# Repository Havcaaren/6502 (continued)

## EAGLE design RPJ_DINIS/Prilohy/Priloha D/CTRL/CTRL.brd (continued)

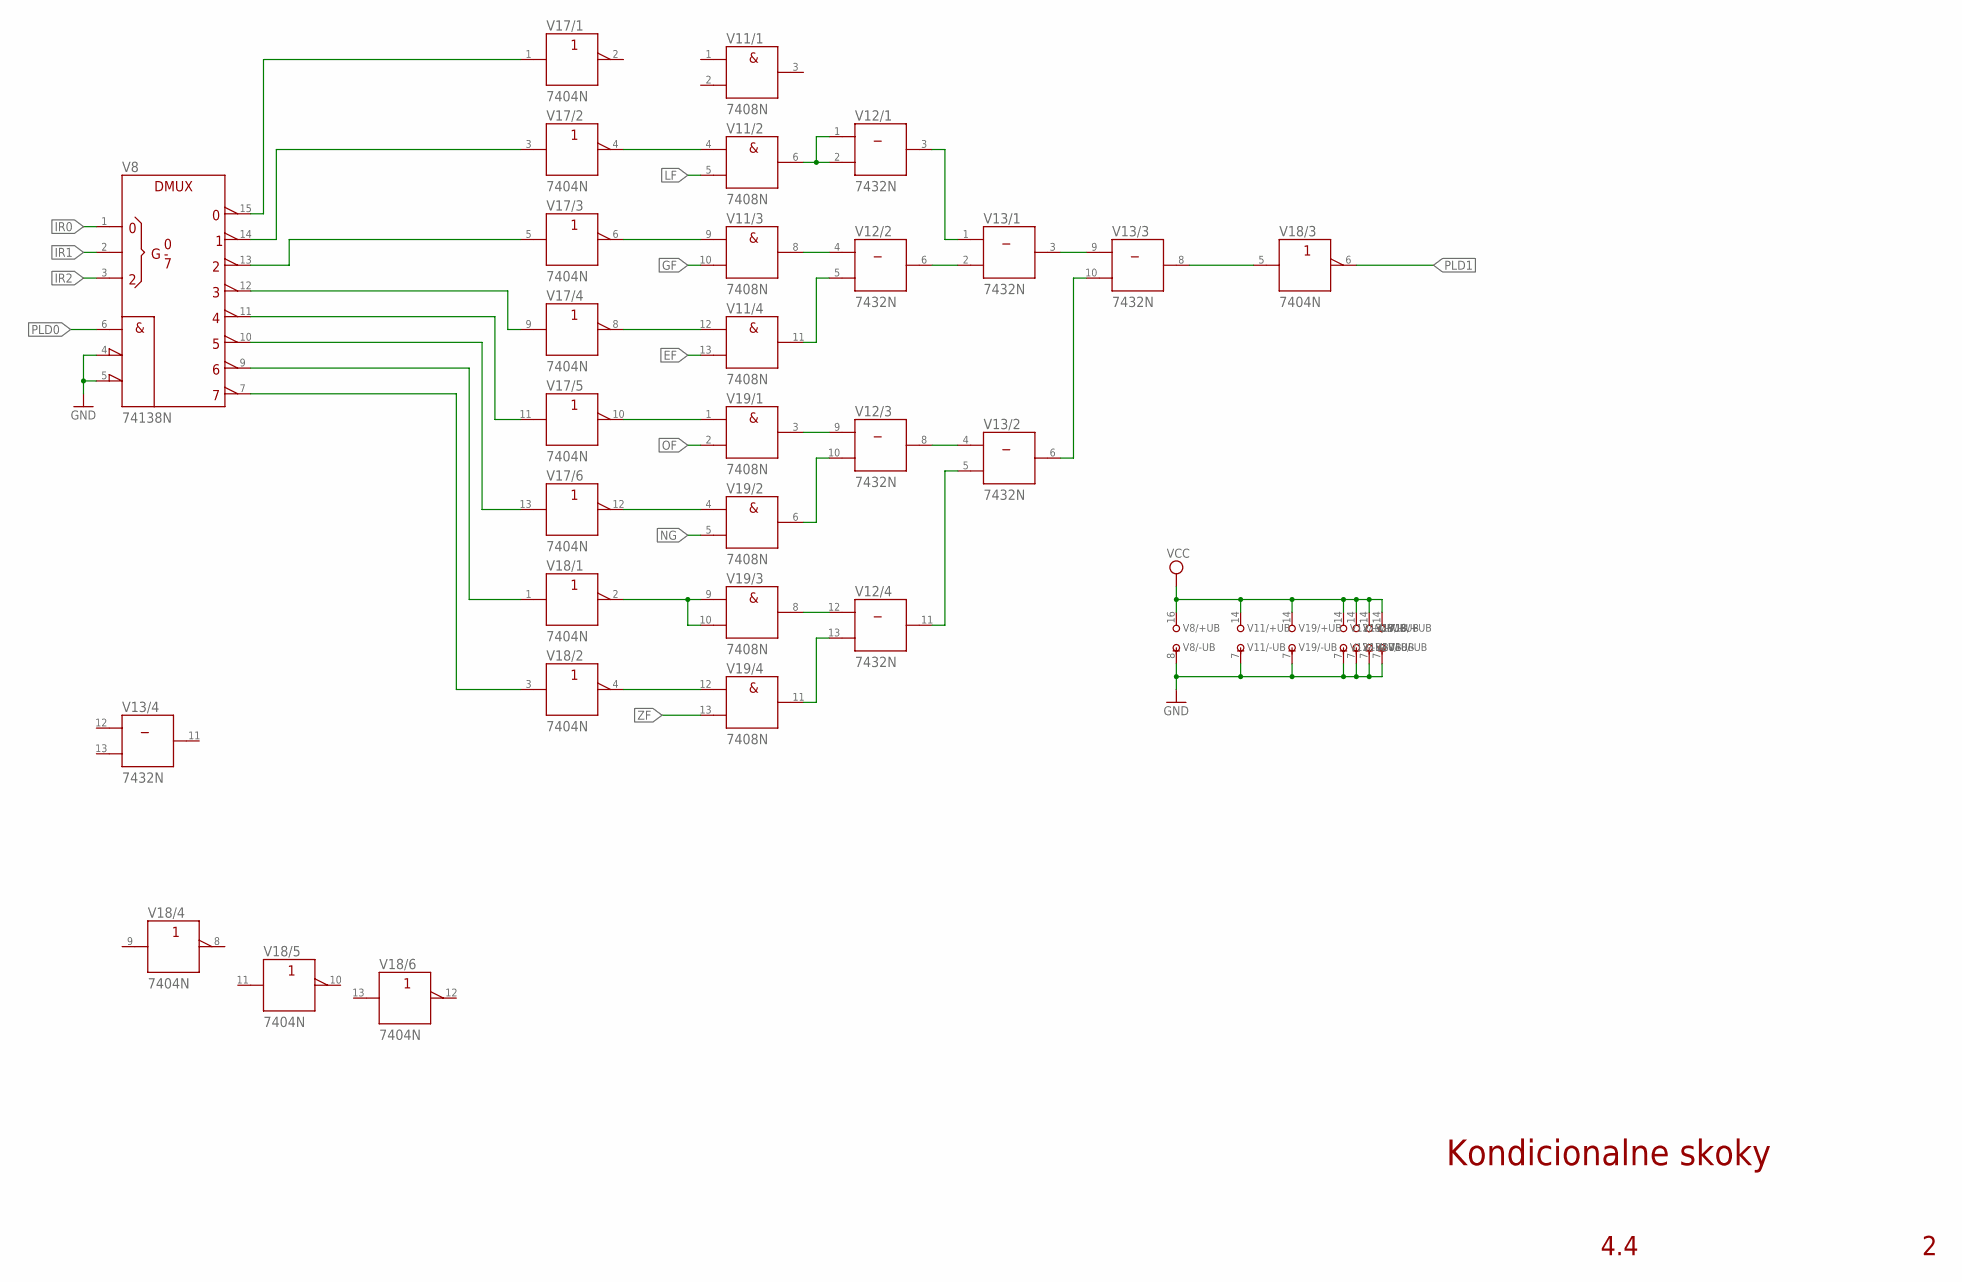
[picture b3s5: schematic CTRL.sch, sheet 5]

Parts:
V8: 74138N; DIL16
V11, V19: 7408N; DIL14
V12, V13: 7432N; DIL14
V17, V18: 7404N; DIL14

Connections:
EF: V11.13 (B); also elsewhere on the board
GF: V11.10 (B); also elsewhere on the board
GND: V8.4 (!G2A), V8.5 (!G2B), V8.8 (-UB), V11.7 (-UB), V12.7 (-UB), V13.7 (-UB), V17.7 (-UB), V18.7 (-UB), V19.7 (-UB); also elsewhere on the board
IR0: V8.1 (A); also elsewhere on the board
IR1: V8.2 (B); also elsewhere on the board
IR2: V8.3 (C); also elsewhere on the board
LF: V11.5 (B); also elsewhere on the board
unnamed: V18.2 (Y), V19.9 (A), V19.10 (B)
unnamed: V18.4 (Y), V19.12 (A)
unnamed: V17.12 (Y), V19.4 (A)
unnamed: V17.10 (Y), V19.1 (A)
unnamed: V11.12 (A), V17.8 (Y)
unnamed: V11.9 (A), V17.6 (Y)
unnamed: V11.4 (A), V17.4 (Y)
unnamed: V8.15 (Y0), V17.1 (A)
unnamed: V8.14 (Y1), V17.3 (A)
unnamed: V8.13 (Y2), V17.5 (A)
unnamed: V8.12 (Y3), V17.9 (A)
unnamed: V8.11 (Y4), V17.11 (A)
unnamed: V8.10 (Y5), V17.13 (A)
unnamed: V8.9 (Y6), V18.1 (A)
unnamed: V8.7 (Y7), V18.3 (A)
unnamed: V13.8 (Y), V18.5 (A)
unnamed: V12.11 (Y), V13.5 (B)
unnamed: V12.8 (Y), V13.4 (A)
unnamed: V12.3 (Y), V13.1 (A)
unnamed: V12.6 (Y), V13.2 (B)
unnamed: V13.3 (Y), V13.9 (A)
unnamed: V13.6 (Y), V13.10 (B)
unnamed: V11.6 (Y), V12.1 (A), V12.2 (B)
unnamed: V11.8 (Y), V12.4 (A)
unnamed: V11.11 (Y), V12.5 (B)
unnamed: V12.9 (A), V19.3 (Y)
unnamed: V12.10 (B), V19.6 (Y)
unnamed: V12.13 (B), V19.11 (Y)
unnamed: V12.12 (A), V19.8 (Y)
NG: V19.5 (B); also elsewhere on the board
OF: V19.2 (B); also elsewhere on the board
PLD0: V8.6 (G1); also elsewhere on the board
PLD1: V18.6 (Y); also elsewhere on the board
VCC: V8.16 (+UB), V11.14 (+UB), V12.14 (+UB), V13.14 (+UB), V17.14 (+UB), V18.14 (+UB), V19.14 (+UB); also elsewhere on the board
ZF: V19.13 (B); also elsewhere on the board

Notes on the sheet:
4.4
Kondicionalne skoky

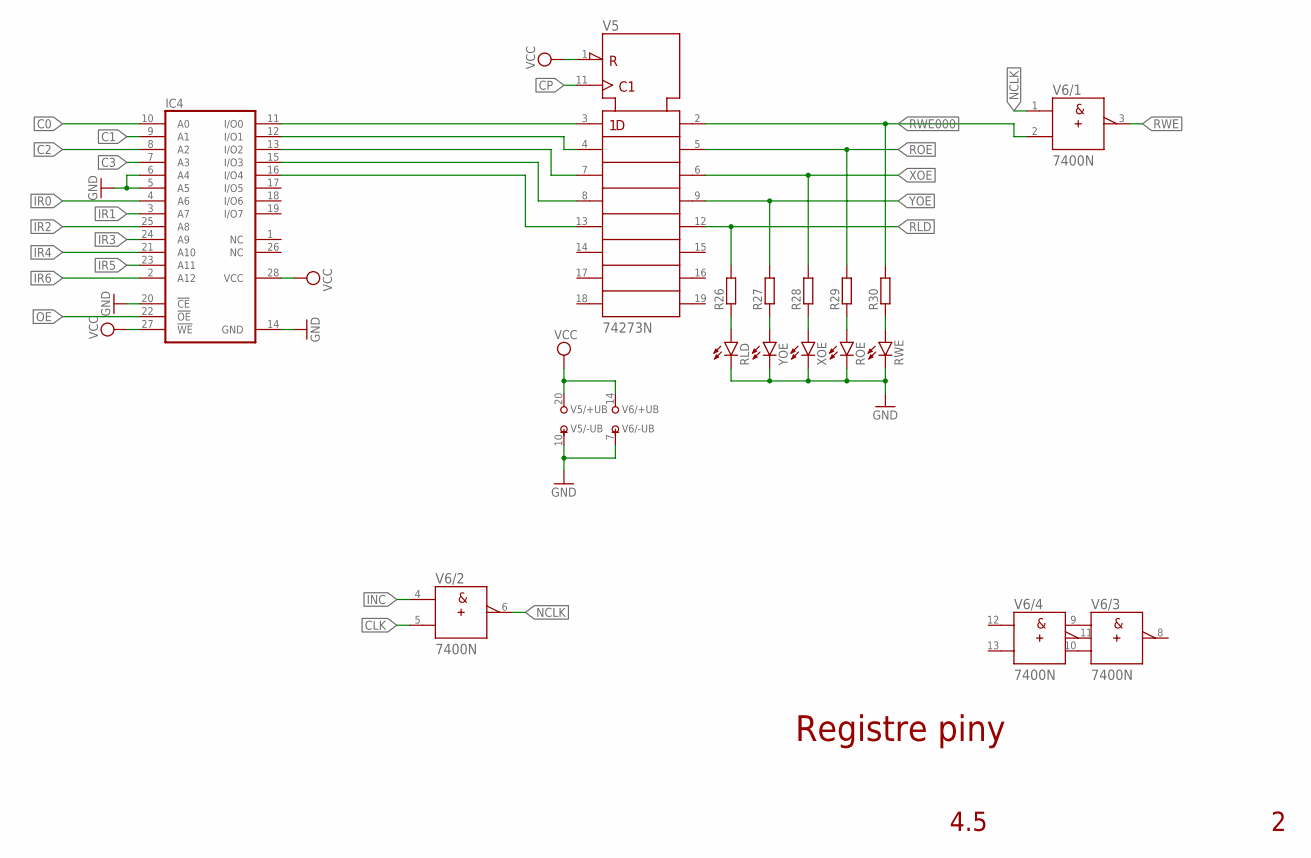
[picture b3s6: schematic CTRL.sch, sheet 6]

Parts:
IC4: 28C64C; DIL28-6
R26, R27, R28, R29, R30: R-EU_0204/7; 0204/7
RLD: LED5MM
ROE: LED5MM
RWE: LED5MM
V5: 74273N; DIL20
V6: 7400N; DIL14
XOE: LED5MM
YOE: LED5MM

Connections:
C0: IC4.10 (A0); also elsewhere on the board
C1: IC4.9 (A1); also elsewhere on the board
C2: IC4.8 (A2); also elsewhere on the board
C3: IC4.7 (A3); also elsewhere on the board
CLK: V6.5 (B); also elsewhere on the board
CP: V5.11 (CLK); also elsewhere on the board
GND: IC4.5 (A5), IC4.6 (A4), IC4.14 (GND), IC4.20 (!CE), RLD.K (C), ROE.K (C), RWE.K (C), V5.10 (-UB), V6.7 (-UB), XOE.K (C), YOE.K (C); also elsewhere on the board
INC: V6.4 (A); also elsewhere on the board
IR0: IC4.4 (A6); also elsewhere on the board
IR1: IC4.3 (A7); also elsewhere on the board
IR2: IC4.25 (A8); also elsewhere on the board
IR3: IC4.24 (A9); also elsewhere on the board
IR4: IC4.21 (A10); also elsewhere on the board
IR5: IC4.23 (A11); also elsewhere on the board
IR6: IC4.2 (A12); also elsewhere on the board
unnamed: IC4.16 (I/O4), V5.13 (5D)
unnamed: R26.1, RLD.A
unnamed: R27.1, YOE.A
unnamed: R28.1, XOE.A
unnamed: R29.1, ROE.A
unnamed: R30.1, RWE.A
NCLK: V6.1 (A), V6.6 (Y); also elsewhere on the board
OE: IC4.22 (!OE); also elsewhere on the board
RLD: R26.2, V5.12 (5Q); also elsewhere on the board
ROE: R29.2, V5.5 (2Q); also elsewhere on the board
RWE: V6.3 (Y); also elsewhere on the board
RWE000: R30.2, V5.2 (1Q), V6.2 (B)
VCC: IC4.27 (!WE), IC4.28 (VCC), V5.1 (!CLR), V5.20 (+UB), V6.14 (+UB); also elsewhere on the board
XCP0: IC4.11 (I/O0), V5.3 (1D)
XOE: R28.2, V5.6 (3Q); also elsewhere on the board
XOE0: IC4.12 (I/O1), V5.4 (2D)
YCP0: IC4.13 (I/O2), V5.7 (3D)
YOE: R27.2, V5.9 (4Q); also elsewhere on the board
YOE0: IC4.15 (I/O3), V5.8 (4D)

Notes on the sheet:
4.5
Registre piny

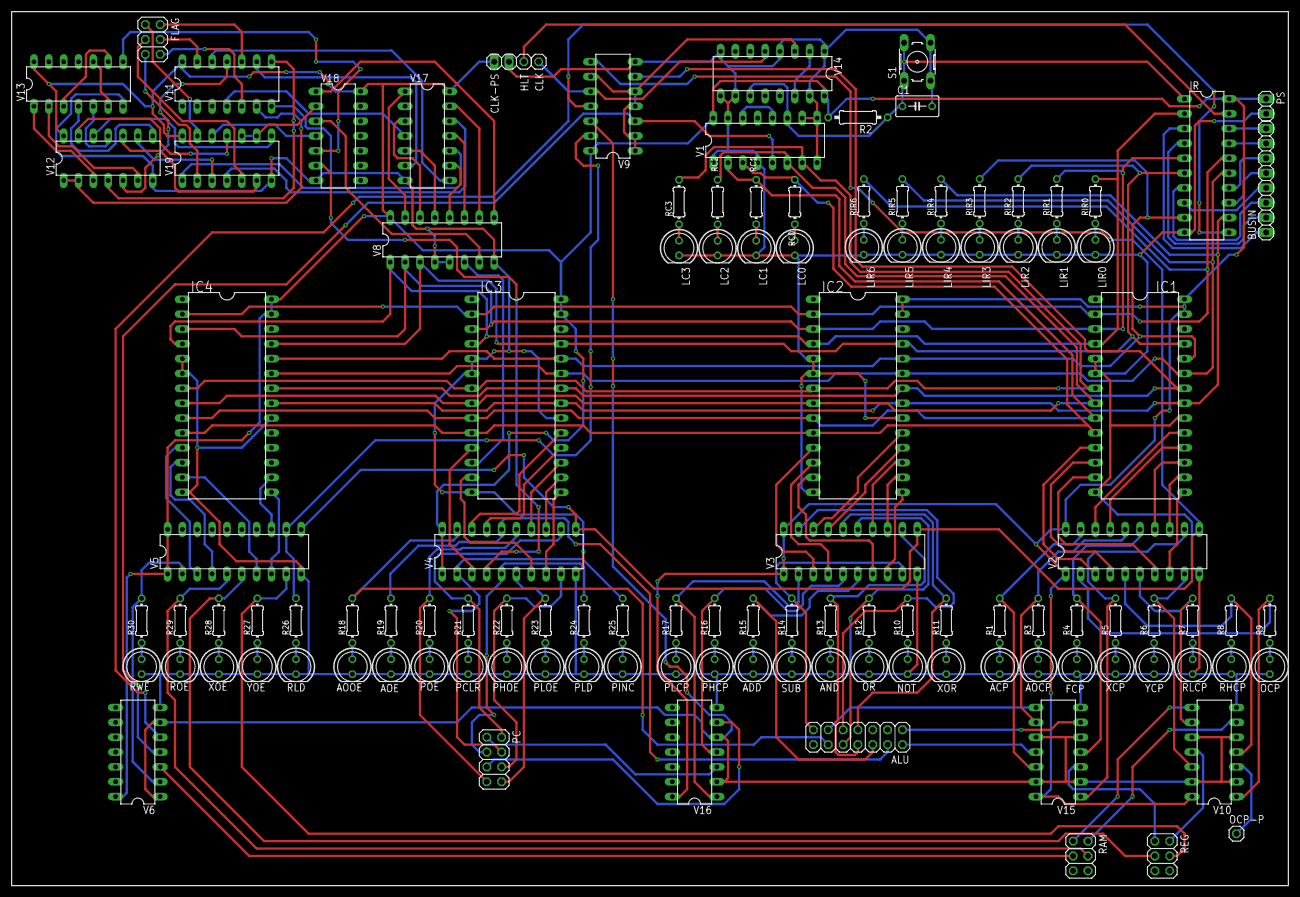
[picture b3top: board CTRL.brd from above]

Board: 2 copper layers, 218.4 x 149.5 mm, 117 parts (0 on the bottom side), 177 nets.

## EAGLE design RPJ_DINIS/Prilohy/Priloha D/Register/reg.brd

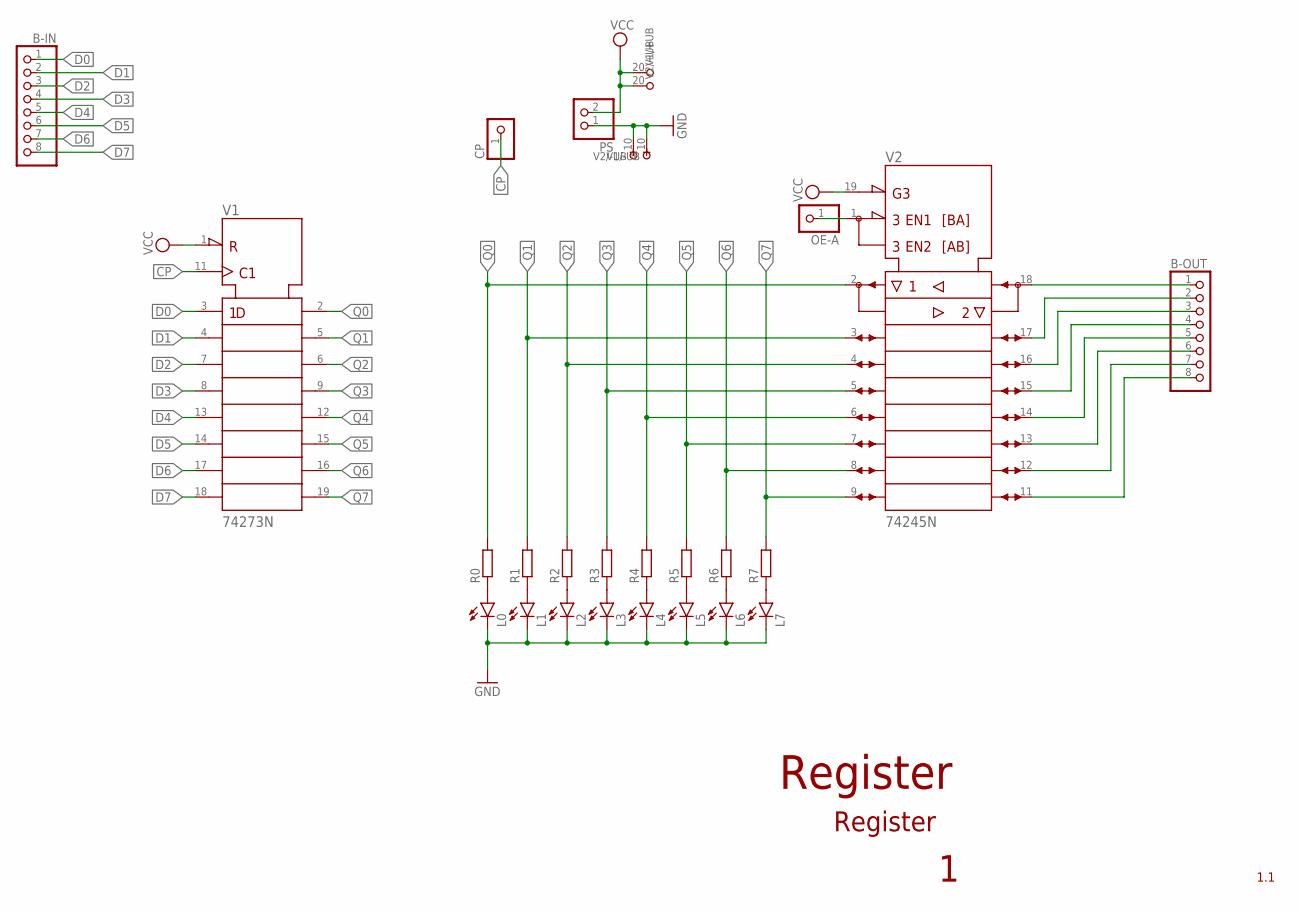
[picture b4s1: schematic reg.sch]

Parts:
B-IN: PINHD-1X8; 1X08
B-OUT: PINHD-1X8; 1X08
CP: PINHD-1X1; 1X01
L0, L1, L2, L3, L4, L5, L6, L7: LED5MM
OE-A: PINHD-1X1; 1X01
PS: PINHD-1X2; 1X02
R0, R1, R2, R3, R4, R5, R6, R7: R-EU_0204/7; 0204/7
V1: 74273N; DIL20
V2: 74245N; DIL20

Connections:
BO0: B-OUT.8, V2.11 (B8)
BO1: B-OUT.7, V2.12 (B7)
BO2: B-OUT.6, V2.13 (B6)
BO3: B-OUT.5, V2.14 (B5)
BO4: B-OUT.4, V2.15 (B4)
BO5: B-OUT.3, V2.16 (B3)
BO6: B-OUT.2, V2.17 (B2)
BO7: B-OUT.1, V2.18 (B1)
CP: CP.1, V1.11 (CLK)
D0: B-IN.1, V1.3 (1D)
D1: B-IN.2, V1.4 (2D)
D2: B-IN.3, V1.7 (3D)
D3: B-IN.4, V1.8 (4D)
D4: B-IN.5, V1.13 (5D)
D5: B-IN.6, V1.14 (6D)
D6: B-IN.7, V1.17 (7D)
D7: B-IN.8, V1.18 (8D)
GND: L0.K (C), L1.K (C), L2.K (C), L3.K (C), L4.K (C), L5.K (C), L6.K (C), L7.K (C), PS.1, V1.10 (-UB), V2.10 (-UB)
unnamed: L7.A, R7.1
unnamed: L6.A, R6.1
unnamed: L5.A, R5.1
unnamed: L4.A, R4.1
unnamed: L3.A, R3.1
unnamed: L2.A, R2.1
unnamed: L1.A, R1.1
unnamed: L0.A, R0.1
unnamed: OE-A.1, V2.1 (DIR)
Q0: R0.2, V1.2 (1Q), V2.2 (A1)
Q1: R1.2, V1.5 (2Q), V2.3 (A2)
Q2: R2.2, V1.6 (3Q), V2.4 (A3)
Q3: R3.2, V1.9 (4Q), V2.5 (A4)
Q4: R4.2, V1.12 (5Q), V2.6 (A5)
Q5: R5.2, V1.15 (6Q), V2.7 (A6)
Q6: R6.2, V1.16 (7Q), V2.8 (A7)
Q7: R7.2, V1.19 (8Q), V2.9 (A8)
VCC: PS.2, V1.1 (!CLR), V1.20 (+UB), V2.19 (!G), V2.20 (+UB)

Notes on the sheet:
1.1
Register

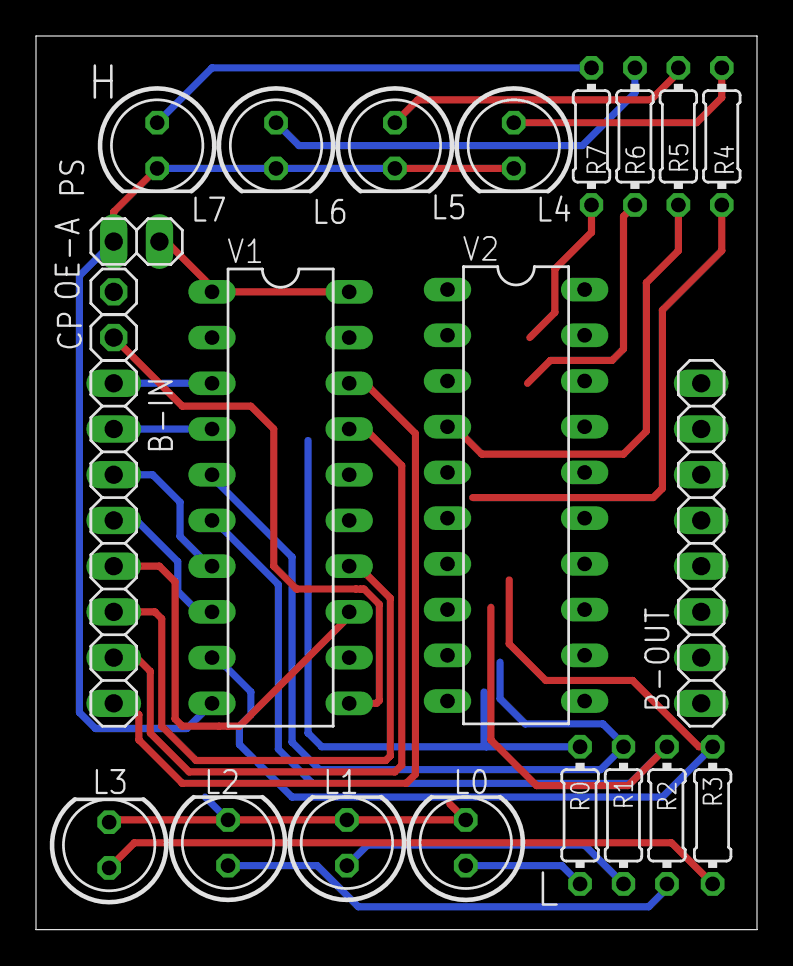
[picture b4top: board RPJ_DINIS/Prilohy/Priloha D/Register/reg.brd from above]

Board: 2 copper layers, 40.1 x 49.6 mm, 23 parts (0 on the bottom side), 36 nets.

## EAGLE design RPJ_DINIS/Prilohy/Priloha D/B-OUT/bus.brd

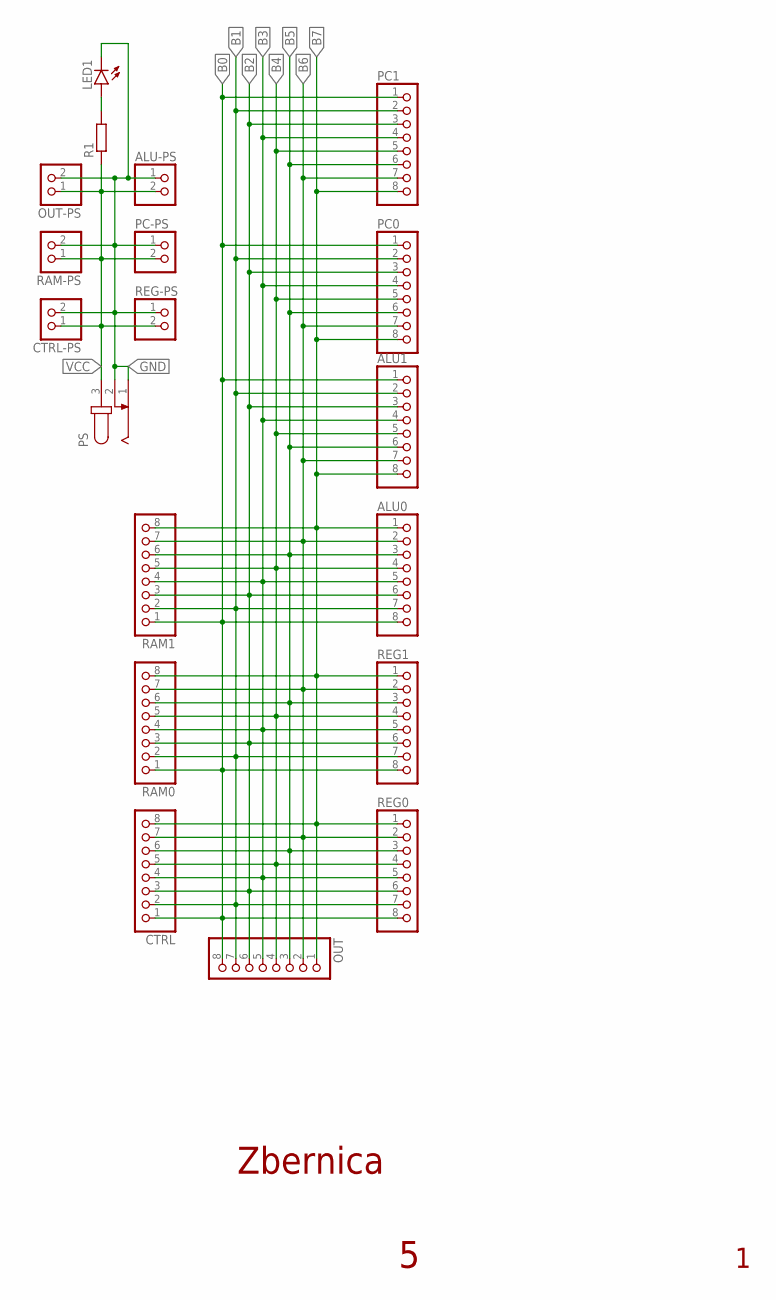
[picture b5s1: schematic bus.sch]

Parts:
ALU0, ALU1: PINHD-1X8; 1X08
ALU-PS: PINHD-1X2; 1X02
CTRL: PINHD-1X8; 1X08
CTRL-PS: PINHD-1X2; 1X02
LED1: LED5MM
OUT: PINHD-1X8; 1X08
OUT-PS: PINHD-1X2; 1X02
PC0, PC1: PINHD-1X8; 1X08
PC-PS: PINHD-1X2; 1X02
PS: JACK-PLUG0; SPC4077
R1: R-EU_0204/7; 0204/7
RAM0, RAM1: PINHD-1X8; 1X08
RAM-PS: PINHD-1X2; 1X02
REG0, REG1: PINHD-1X8; 1X08
REG-PS: PINHD-1X2; 1X02

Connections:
B0: ALU0.8, ALU1.1, CTRL.1, OUT.8, PC0.1, PC1.1, RAM0.1, RAM1.1, REG0.8, REG1.8
B1: ALU0.7, ALU1.2, CTRL.2, OUT.7, PC0.2, PC1.2, RAM0.2, RAM1.2, REG0.7, REG1.7
B2: ALU0.6, ALU1.3, CTRL.3, OUT.6, PC0.3, PC1.3, RAM0.3, RAM1.3, REG0.6, REG1.6
B3: ALU0.5, ALU1.4, CTRL.4, OUT.5, PC0.4, PC1.4, RAM0.4, RAM1.4, REG0.5, REG1.5
B4: ALU0.4, ALU1.5, CTRL.5, OUT.4, PC0.5, PC1.5, RAM0.5, RAM1.5, REG0.4, REG1.4
B5: ALU0.3, ALU1.6, CTRL.6, OUT.3, PC0.6, PC1.6, RAM0.6, RAM1.6, REG0.3, REG1.3
B6: ALU0.2, ALU1.7, CTRL.7, OUT.2, PC0.7, PC1.7, RAM0.7, RAM1.7, REG0.2, REG1.2
B7: ALU0.1, ALU1.8, CTRL.8, OUT.1, PC0.8, PC1.8, RAM0.8, RAM1.8, REG0.1, REG1.1
GND: ALU-PS.1, CTRL-PS.2, LED1.K (C), OUT-PS.2, PC-PS.1, PS.1, PS.2, RAM-PS.2, REG-PS.1
unnamed: LED1.A, R1.2
VCC: ALU-PS.2, CTRL-PS.1, OUT-PS.1, PC-PS.2, PS.3, R1.1, RAM-PS.1, REG-PS.2

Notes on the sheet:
Zbernica

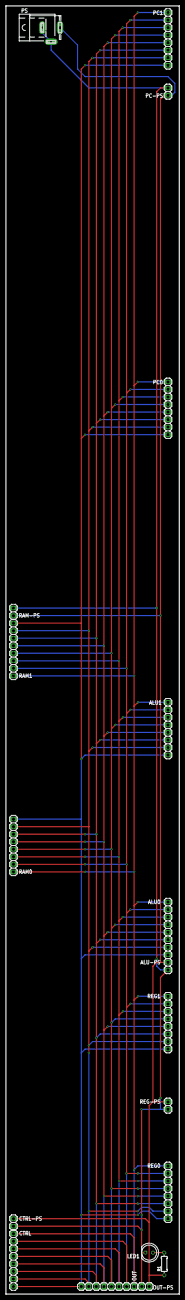
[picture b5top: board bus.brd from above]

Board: 2 copper layers, 58.4 x 434.0 mm, 19 parts (0 on the bottom side), 11 nets.

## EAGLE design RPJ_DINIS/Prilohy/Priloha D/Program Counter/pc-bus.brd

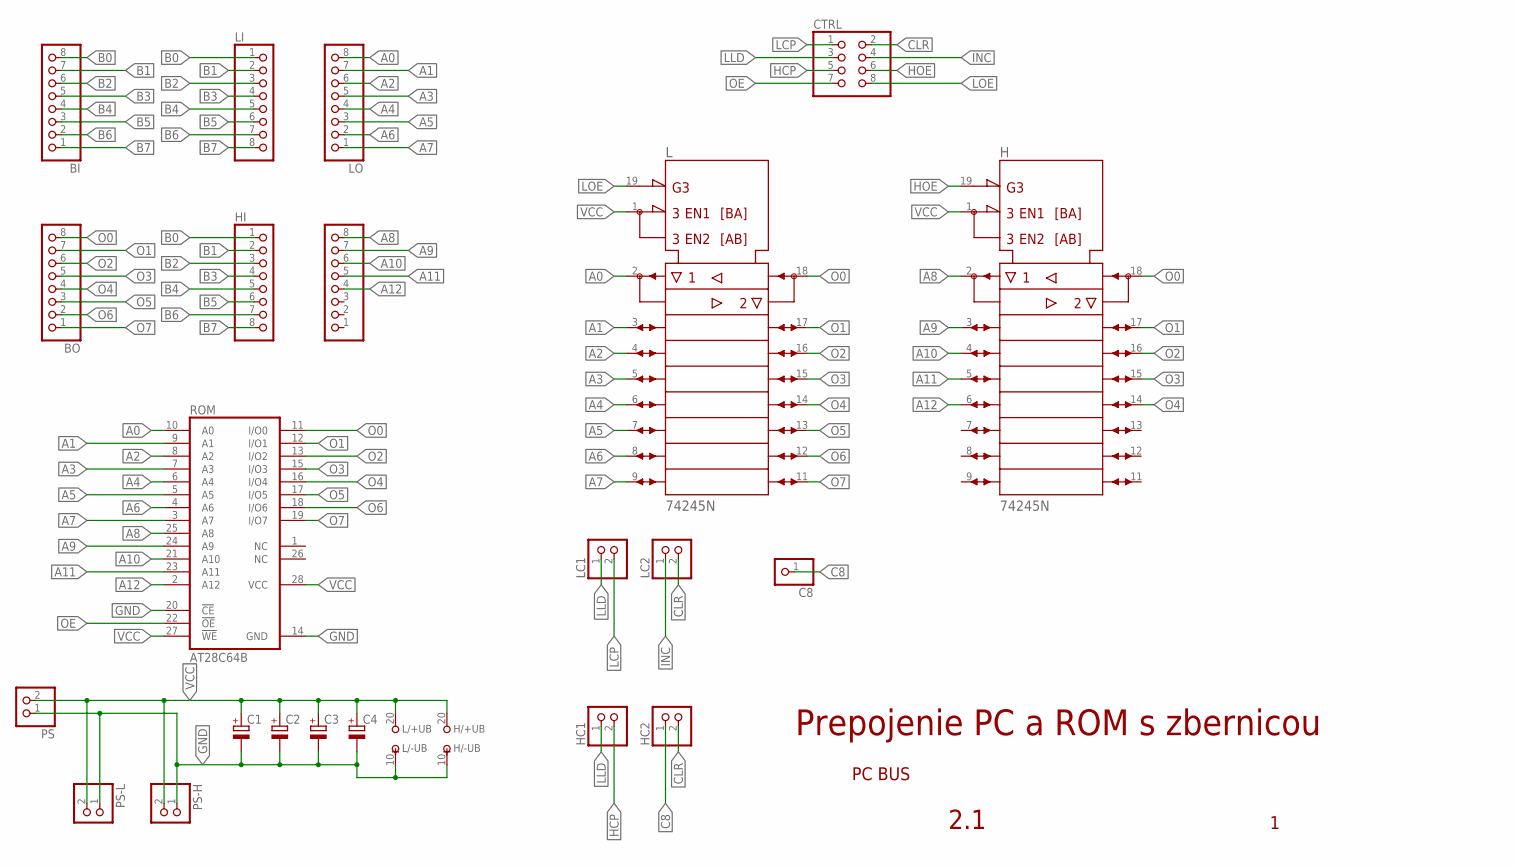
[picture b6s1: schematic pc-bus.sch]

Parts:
BI: PINHD-1X8; 1X08
BO: PINHD-1X8; 1X08
C1, C2, C3, C4: CPOL-EUE2.5-6; E2,5-6
C8: PINHD-1X1; 1X01
CTRL: PINHD-2X4; 2X04
H: 74245N; DIL20
HC1, HC2: PINHD-1X2; 1X02
HI: PINHD-1X8; 1X08
HO: PINHD-1X8; 1X08
L: 74245N; DIL20
LC1, LC2: PINHD-1X2; 1X02
LI: PINHD-1X8; 1X08
LO: PINHD-1X8; 1X08
PS: PINHD-1X2; 1X02
PS-H: PINHD-1X2; 1X02
PS-L: PINHD-1X2; 1X02
ROM: AT28C64B; DIL28-6

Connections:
A0: L.2 (A1), LO.8, ROM.10 (A0)
A1: L.3 (A2), LO.7, ROM.9 (A1)
A2: L.4 (A3), LO.6, ROM.8 (A2)
A3: L.5 (A4), LO.5, ROM.7 (A3)
A4: L.6 (A5), LO.4, ROM.6 (A4)
A5: L.7 (A6), LO.3, ROM.5 (A5)
A6: L.8 (A7), LO.2, ROM.4 (A6)
A7: L.9 (A8), LO.1, ROM.3 (A7)
A8: H.2 (A1), HO.8, ROM.25 (A8)
A9: H.3 (A2), HO.7, ROM.24 (A9)
A10: H.4 (A3), HO.6, ROM.21 (A10)
A11: H.5 (A4), HO.5, ROM.23 (A11)
A12: H.6 (A5), HO.4, ROM.2 (A12)
B0: BI.8, HI.1, LI.1
B1: BI.7, HI.2, LI.2
B2: BI.6, HI.3, LI.3
B3: BI.5, HI.4, LI.4
B4: BI.4, HI.5, LI.5
B5: BI.3, HI.6, LI.6
B6: BI.2, HI.7, LI.7
B7: BI.1, HI.8, LI.8
C8: C8.1, HC2.1
CLR: CTRL.2, HC2.2, LC2.2
GND: C1.-, C2.-, C3.-, C4.-, H.10 (-UB), L.10 (-UB), PS.1, PS-H.1, PS-L.1, ROM.14 (GND), ROM.20 (!CE)
HCP: CTRL.5, HC1.2
HOE: CTRL.6, H.19 (!G)
INC: CTRL.4, LC2.1
LCP: CTRL.1, LC1.2
LLD: CTRL.3, HC1.1, LC1.1
LOE: CTRL.8, L.19 (!G)
O0: BO.8, H.18 (B1), L.18 (B1), ROM.11 (I/O0)
O1: BO.7, H.17 (B2), L.17 (B2), ROM.12 (I/O1)
O2: BO.6, H.16 (B3), L.16 (B3), ROM.13 (I/O2)
O3: BO.5, H.15 (B4), L.15 (B4), ROM.15 (I/O3)
O4: BO.4, H.14 (B5), L.14 (B5), ROM.16 (I/O4)
O5: BO.3, L.13 (B6), ROM.17 (I/O5)
O6: BO.2, L.12 (B7), ROM.18 (I/O6)
O7: BO.1, L.11 (B8), ROM.19 (I/O7)
OE: CTRL.7, ROM.22 (!OE)
VCC: C1.+, C2.+, C3.+, C4.+, H.1 (DIR), H.20 (+UB), L.1 (DIR), L.20 (+UB), PS.2, PS-H.2, PS-L.2, ROM.27 (!WE), ROM.28 (VCC)

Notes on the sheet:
Prepojenie PC a ROM s zbernicou
PC BUS
2.1

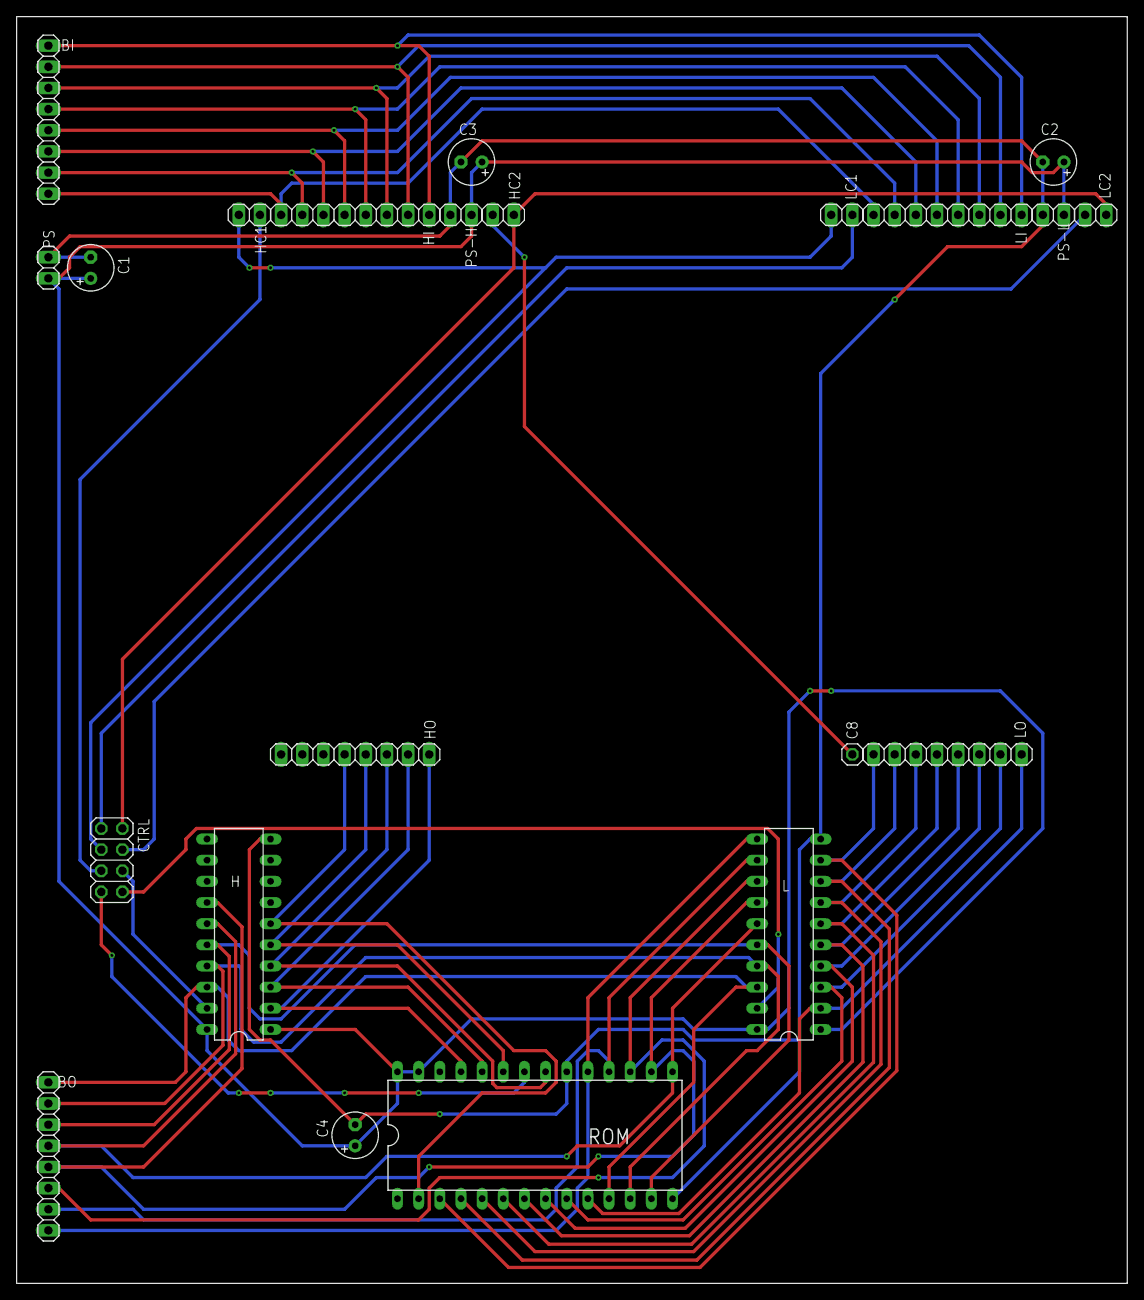
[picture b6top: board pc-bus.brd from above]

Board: 2 copper layers, 133.3 x 152.1 mm, 22 parts (0 on the bottom side), 40 nets.

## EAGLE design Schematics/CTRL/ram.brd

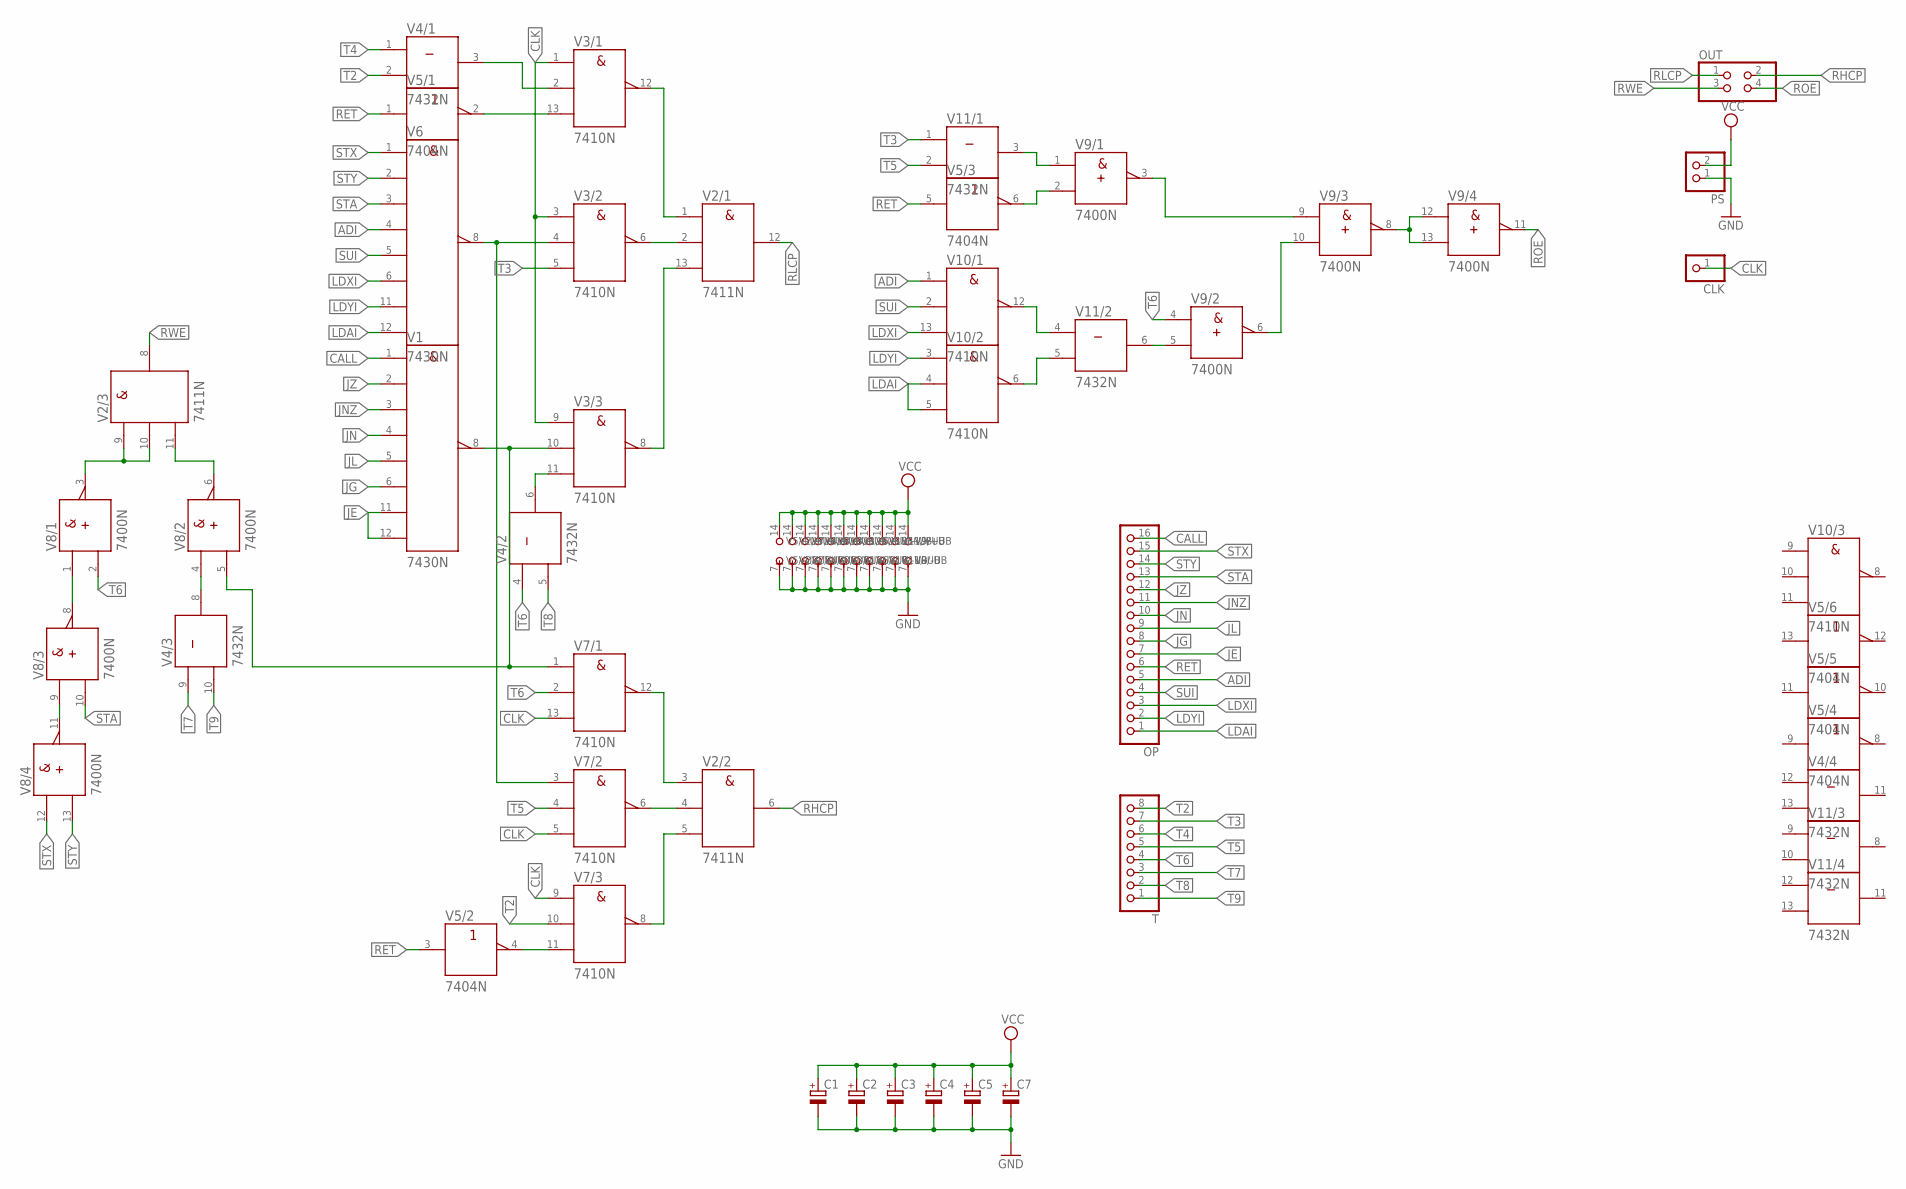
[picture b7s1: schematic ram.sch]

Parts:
C1, C2, C3, C4, C5, C7: CPOL-EUE2.5-6; E2,5-6
CLK: PINHD-1X1; 1X01
OP: PINHD-1X16; 1X16
OUT: PINHD-2X2; 2X02
PS: PINHD-1X2; 1X02
T: PINHD-1X8; 1X08
V1, V6: 7430N; DIL14
V2: 7411N; DIL14
V3, V7, V10: 7410N; DIL14
V4, V11: 7432N; DIL14
V5: 7404N; DIL14
V8, V9: 7400N; DIL14

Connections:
ADI: OP.5, V6.4 (D), V10.1 (A)
CALL: OP.16, V1.1 (A)
CLK: CLK.1, V3.1 (A), V3.3 (A), V3.9 (A), V7.5 (C), V7.9 (A), V7.13 (C)
GND: C1.-, C2.-, C3.-, C4.-, C5.-, C7.-, PS.1, V1.7 (-UB), V2.7 (-UB), V3.7 (-UB), V4.7 (-UB), V5.7 (-UB), V6.7 (-UB), V7.7 (-UB), V8.7 (-UB), V9.7 (-UB), V10.7 (-UB), V11.7 (-UB)
JE: OP.7, V1.11 (G), V1.12 (H)
JG: OP.8, V1.6 (F)
JL: OP.9, V1.5 (E)
JN: OP.10, V1.4 (D)
JNZ: OP.11, V1.3 (C)
JZ: OP.12, V1.2 (B)
LDAI: OP.1, V6.12 (H), V10.4 (B), V10.5 (C)
LDXI: OP.3, V6.6 (F), V10.13 (C)
LDYI: OP.2, V6.11 (G), V10.3 (A)
unnamed: V2.5 (C), V7.8 (Y)
unnamed: V2.2 (B), V3.6 (Y)
unnamed: V2.1 (A), V3.12 (Y)
unnamed: V2.13 (C), V3.8 (Y)
unnamed: V3.2 (B), V4.3 (Y)
unnamed: V3.13 (C), V5.2 (Y)
unnamed: V3.4 (B), V6.8 (Y), V7.3 (A)
unnamed: V9.1 (A), V11.3 (Y)
unnamed: V2.4 (B), V7.6 (Y)
unnamed: V3.11 (C), V4.6 (Y)
unnamed: V2.3 (A), V7.12 (Y)
unnamed: V2.9 (A), V2.10 (B), V8.3 (Y)
unnamed: V2.11 (C), V8.6 (Y)
unnamed: V5.4 (Y), V7.11 (C)
unnamed: V9.3 (Y), V9.9 (A)
unnamed: V9.5 (B), V11.6 (Y)
unnamed: V8.9 (A), V8.11 (Y)
unnamed: V4.8 (Y), V8.4 (A)
unnamed: V8.1 (A), V8.8 (Y)
unnamed: V1.8 (Y), V3.10 (B), V7.1 (A), V8.5 (B)
unnamed: V5.6 (Y), V9.2 (B)
unnamed: V9.8 (Y), V9.12 (A), V9.13 (B)
unnamed: V10.6 (Y), V11.5 (B)
unnamed: V10.12 (Y), V11.4 (A)
unnamed: V9.6 (Y), V9.10 (B)
RET: OP.6, V5.1 (A), V5.3 (A), V5.5 (A)
RHCP: OUT.2, V2.6 (Y)
RLCP: OUT.1, V2.12 (Y)
ROE: OUT.4, V9.11 (Y)
RWE: OUT.3, V2.8 (Y)
STA: OP.13, V6.3 (C), V8.10 (B)
STX: OP.15, V6.1 (A), V8.12 (A)
STY: OP.14, V6.2 (B), V8.13 (B)
SUI: OP.4, V6.5 (E), V10.2 (B)
T2: T.8, V4.2 (B), V7.10 (B)
T3: T.7, V3.5 (C), V11.1 (A)
T4: T.6, V4.1 (A)
T5: T.5, V7.4 (B), V11.2 (B)
T6: T.4, V4.4 (A), V7.2 (B), V8.2 (B), V9.4 (A)
T7: T.3, V4.9 (A)
T8: T.2, V4.5 (B)
T9: T.1, V4.10 (B)
VCC: C1.+, C2.+, C3.+, C4.+, C5.+, C7.+, PS.2, V1.14 (+UB), V2.14 (+UB), V3.14 (+UB), V4.14 (+UB), V5.14 (+UB), V6.14 (+UB), V7.14 (+UB), V8.14 (+UB), V9.14 (+UB), V10.14 (+UB), V11.14 (+UB)

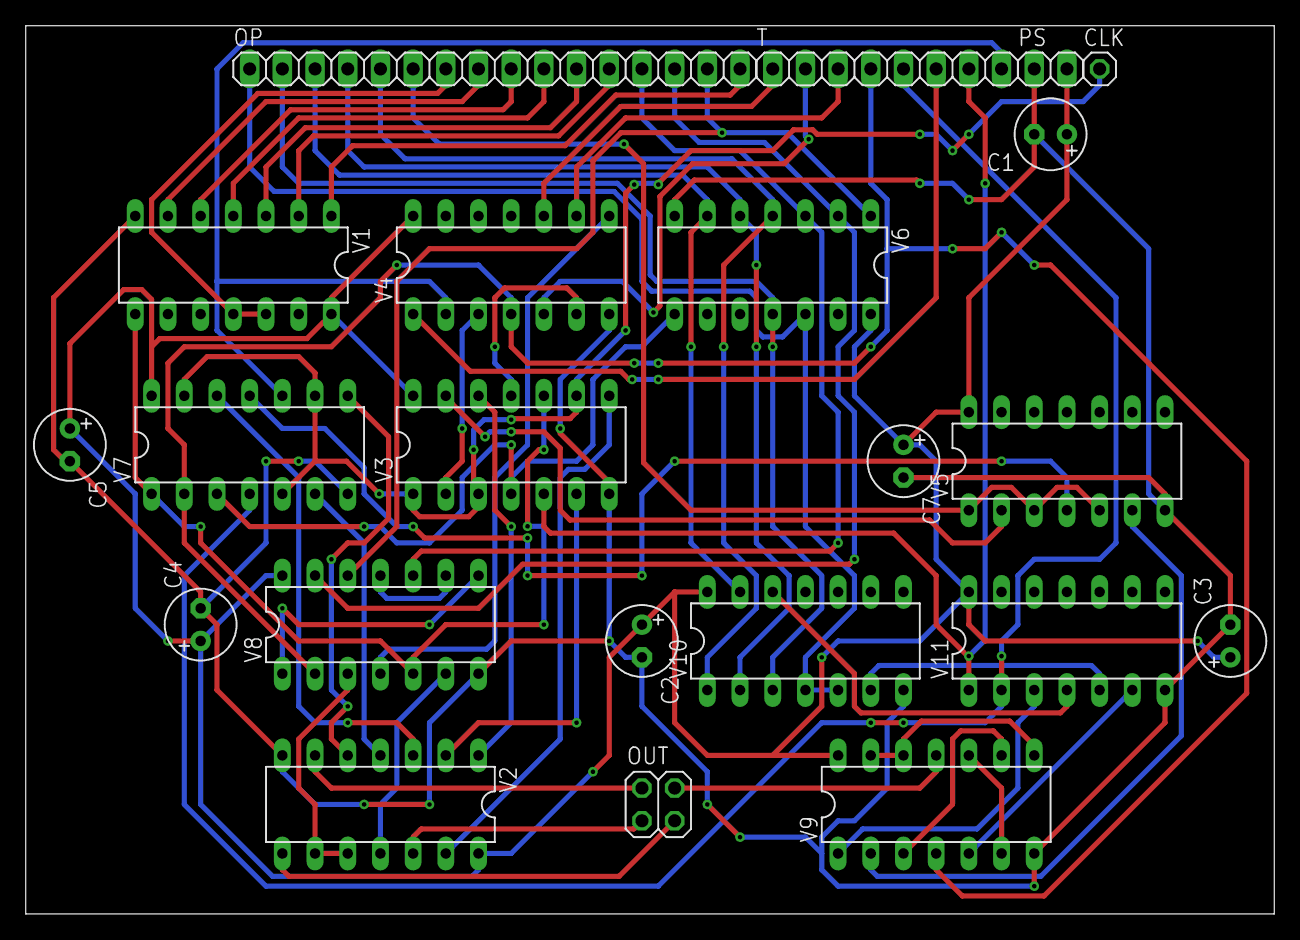
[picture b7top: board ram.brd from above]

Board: 2 copper layers, 97.0 x 69.0 mm, 22 parts (0 on the bottom side), 56 nets.
